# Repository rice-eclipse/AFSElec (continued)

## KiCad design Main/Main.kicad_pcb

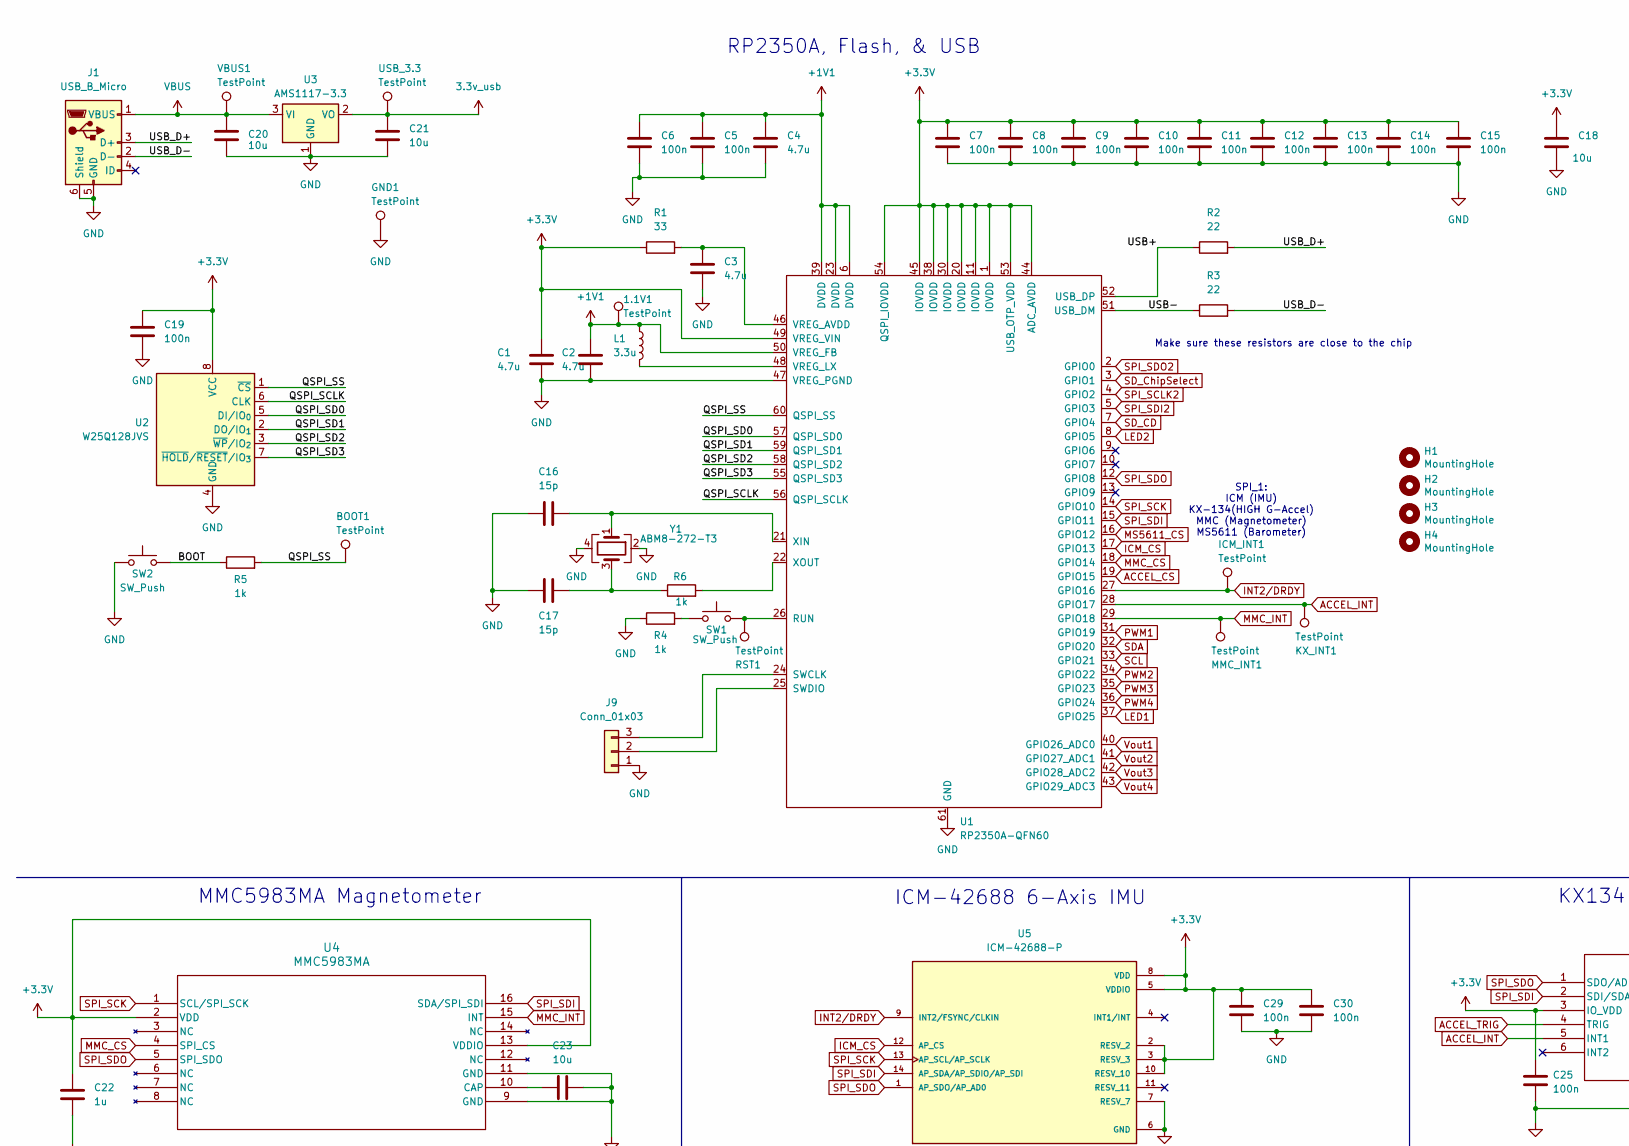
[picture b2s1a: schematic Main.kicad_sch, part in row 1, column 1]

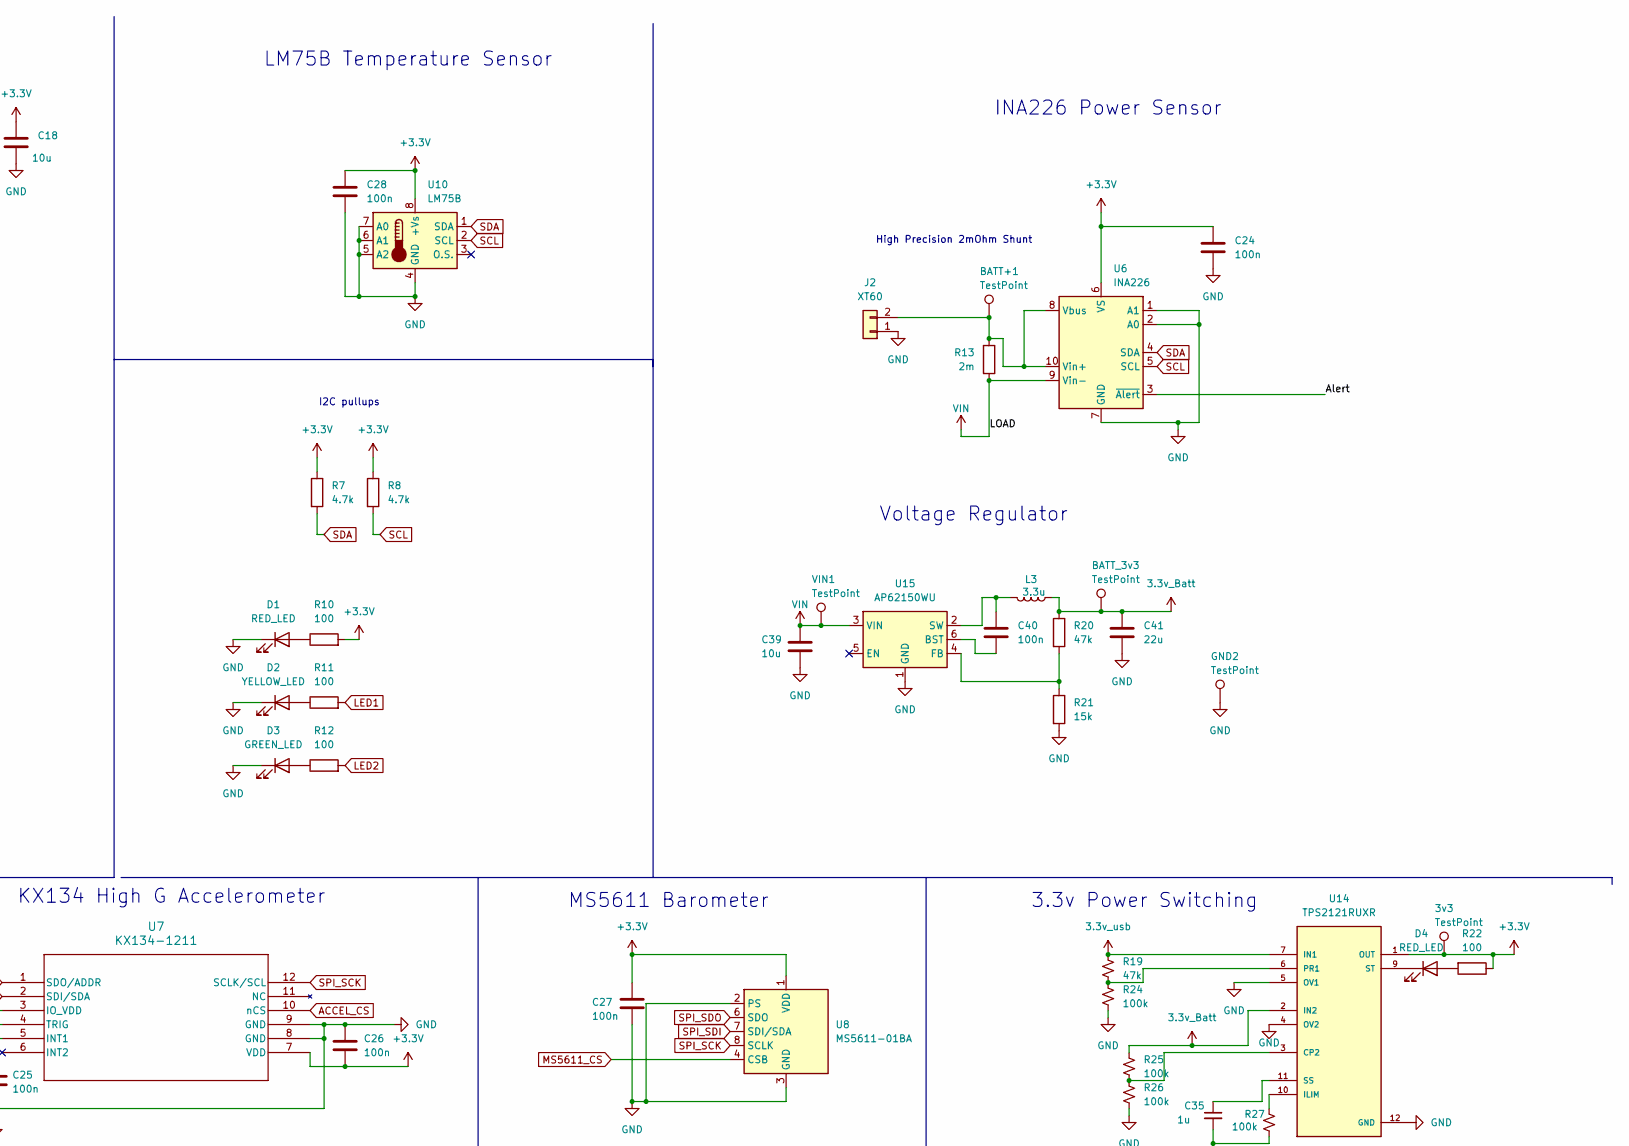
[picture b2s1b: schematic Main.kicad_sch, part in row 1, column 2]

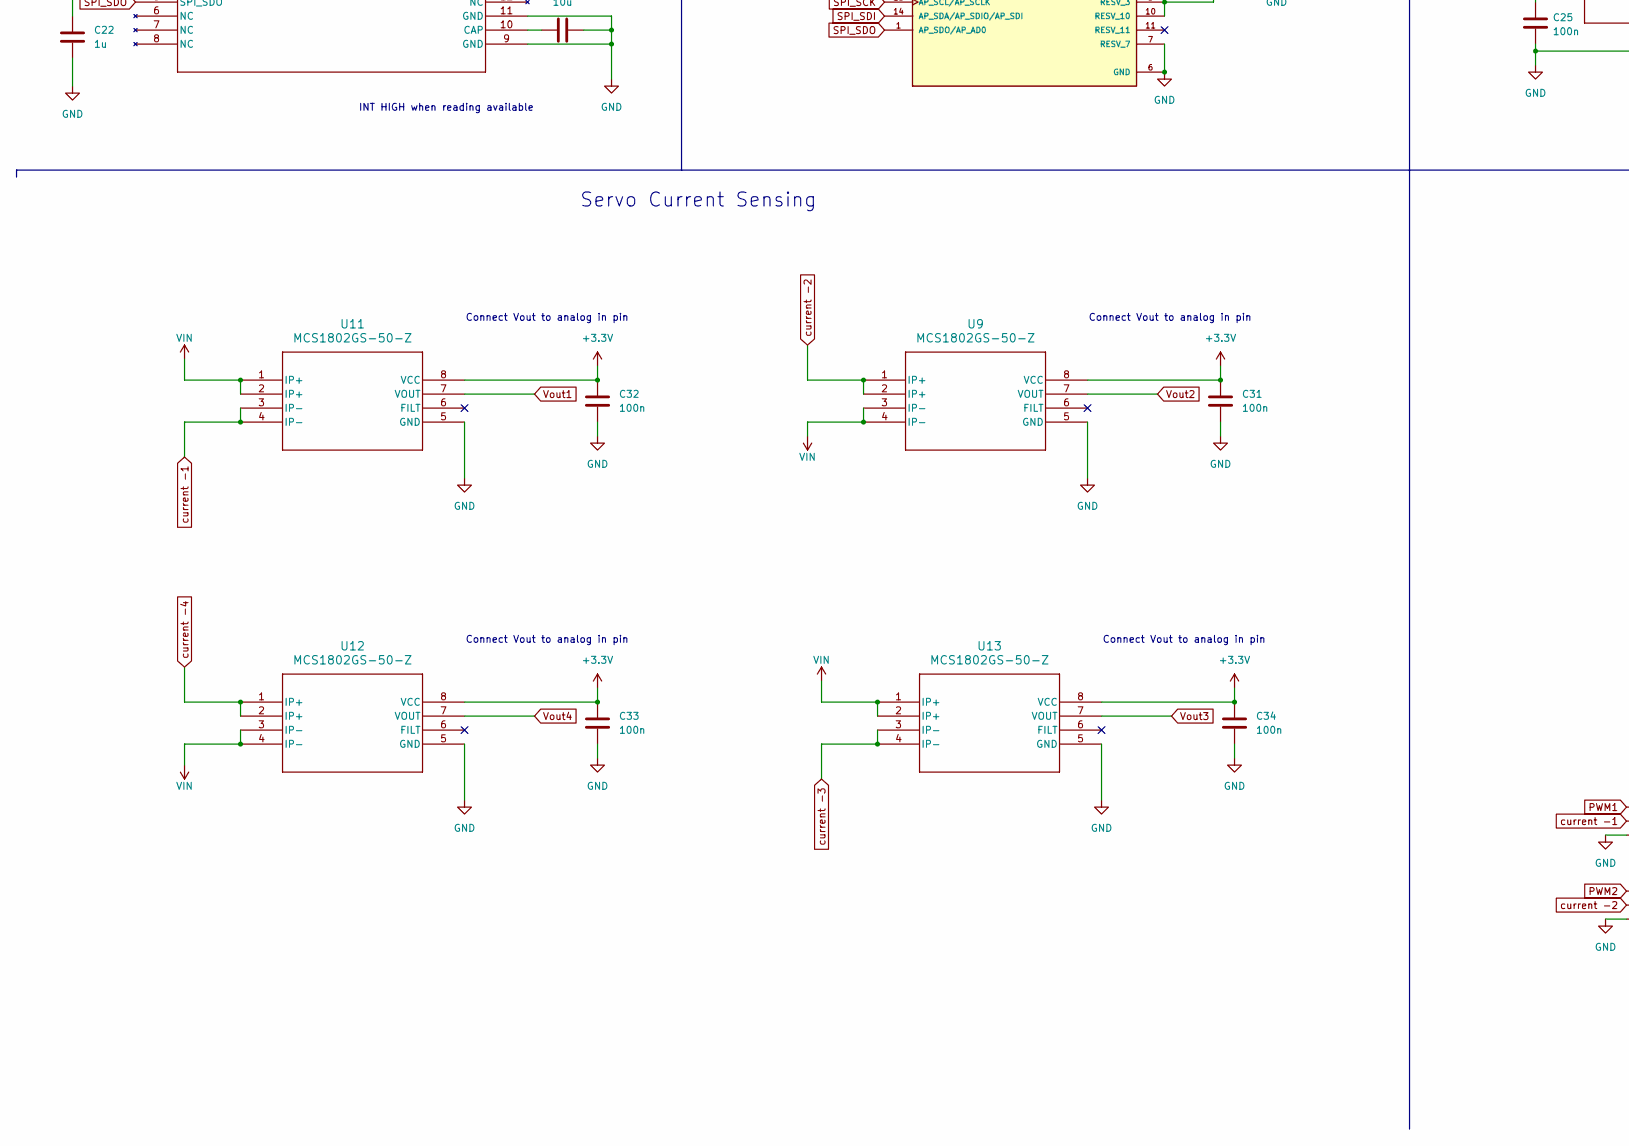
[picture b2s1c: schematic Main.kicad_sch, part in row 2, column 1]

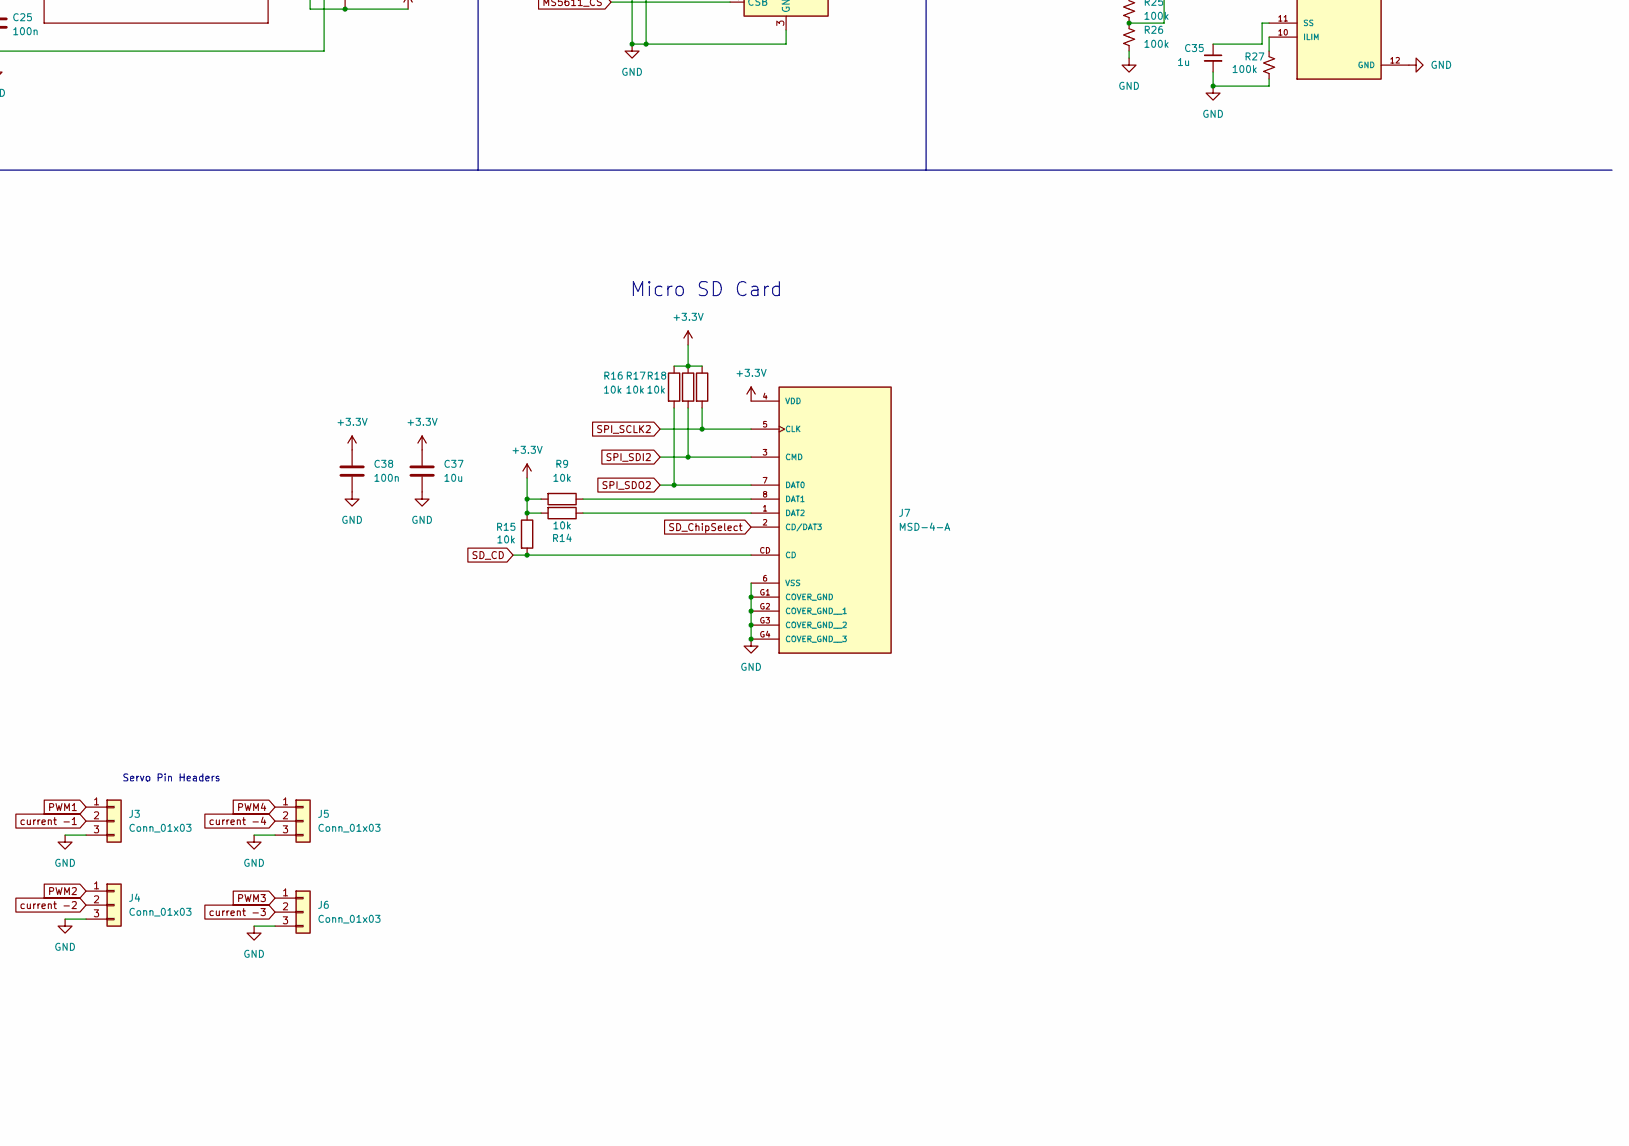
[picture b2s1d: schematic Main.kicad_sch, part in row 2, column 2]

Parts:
1.1V1, 3v3: TestPoint; TestPoint_Pad_D1.0mm
BATT+1: TestPoint; TestPoint_Pad_D1.0mm
BATT_3v3: TestPoint; TestPoint_Pad_D1.0mm
BOOT1: TestPoint; TestPoint_Pad_D1.0mm
C1, C2, C3, C4: 4.7u; C_0402_1005Metric; LCSC Part Number C23733
C5, C6, C7, C8, C9, C10, C11, C12, C13, C14, C15, C19, C24, C25, C26, C27, C28, C29, C30, C31, C32, C33, C34, C38, C40: 100n; C_0402_1005Metric; LCSC Part Number C1525
C16, C17: 15p; C_0402_1005Metric; LCSC Part Number C1548
C18, C20, C21, C23, C37: 10u; C_0805_2012Metric; LCSC Part Number C15850
C22, C35: 1u; C_0805_2012Metric; LCSC Part Number C28323
C39: 10u; C_0805_2012Metric; JLCPCB Part # C15850
C41: 22u; C_0805_2012Metric; LCSC Part Number C45783
D1, D4: RED_LED; LED_0805_2012Metric; LCSC Part Number C84256
D2: YELLOW_LED; LED_0805_2012Metric; LCSC Part Number C2296
D3: GREEN_LED; LED_0805_2012Metric; LCSC Part Number C2297
GND1, GND2: TestPoint; TestPoint_Pad_D1.0mm
H1, H2, H3, H4: MountingHole; MountingHole_3.2mm_M3_ISO14580_Pad
ICM_INT1: TestPoint; TestPoint_Pad_D1.0mm
J1: USB_B_Micro; USB_Micro-B_Amphenol_10118193-0001LF_Horizontal
J2: XT60; AMASS_XT60-M_1x02_P7.20mm_Vertical
J3, J4, J5, J6, J9: Conn_01x03; PinHeader_1x03_P2.54mm_Vertical
J7: MSD-4-A; CUI_MSD-4-A; PARTREV 1.0
KX_INT1: TestPoint; TestPoint_Pad_D1.0mm
L1, L3: 3.3u; AOTA-B201610S3R3-101-T(L_0806_2016metric)
MMC_INT1: TestPoint; TestPoint_Pad_D1.0mm
R1: 33; R_0402_1005Metric; LCSC Part Number C25105
R2, R3: 22; R_0402_1005Metric; LCSC Part Number C25092
R4, R5, R6: 1k; R_0402_1005Metric; LCSC Part Number C11702
R7, R8: 4.7k; R_0402_1005Metric; LCSC Part Number C25900
R9, R14, R15, R16, R17, R18: 10k; R_0402_1005Metric; LCSC Part Number C25744
R10, R11, R12, R22: 100; R_0402_1005Metric; LCSC Part Number C25076
R13: 2m; R_1206_3216Metric
R19, R20: 47k; R_0402_1005Metric; LCSC Part Number C25792
R21: 15k; R_0402_1005Metric; LCSC Part Number C25756
R24, R25, R26, R27: 100k; R_0402_1005Metric; LCSC Part Number C25741
RST1: TestPoint; TestPoint_Pad_D1.0mm
SW1, SW2: SW_Push; SW_Push_SPST_NO_Alps_SKRK
U1: RP2350A-QFN60; QFN-60-1EP_7x7mm_P0.4mm_EP3.4x3.4mm; LCSC Part Number C42411118
U2: W25Q128JVS; SOIC-8_5.3x5.3mm_P1.27mm; LCSC Part Number C97521
U3: AMS1117-3.3; SOT-223-3_TabPin2; LCSC Part Number C6186
U4: MMC5983MA; LGA-16_3x3mm_P0.5mm; LCSC Part Number C404329
U5: ICM-42688-P; LGA-14_3x2.5mm_P0.5mm_LayoutBorder3x4y; PARTREV 1.2; LCSC Part Number C48586483
U6: INA226; VSSOP-10_3x3mm_P0.5mm; LCSC Part Number C49851
U7: KX134-1211; LGA-12_2x2mm_P0.5mm; LCSC Part Number C2157908
U8: MS5611-01BA; LGA-8_3x5mm_P1.25mm; LCSC Part Number C15639
U9, U11, U12, U13: MCS1802GS-50-Z; SOIC-8-1EP_3.9x4.9mm_P1.27mm_EP2.29x3mm; LCSC Part Number C3684509
U10: LM75B; SOIC-8-1EP_3.9x4.9mm_P1.27mm_EP2.29x3mm; LCSC Part Number C34565
U14: TPS2121RUXR; Texas_VQFN-HR-12_2x2.5mm_P0.5mm; LCSC Part Number C485916
U15: AP62150WU; TSOT-23-6; LCSC Part Number C3194237
USB_3.3: TestPoint; TestPoint_Pad_D1.0mm
VBUS1: TestPoint; TestPoint_Pad_D1.0mm
VIN1: TestPoint; TestPoint_Pad_D1.0mm
Y1: ABM8-272-T3; Crystal_SMD_3225-4Pin_3.2x2.5mm; LCSC Part Number C20625731

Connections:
3.3v_Batt: BATT_3v3.1, C41.1, L3.1, R20.1, R25.1, U14.2 (IN2)
3.3v_usb: C21.1, R19.1, U3.2 (VO), U14.7 (IN1), USB_3.3.1
+1V1: 1.1V1.1, C2.1, C4.1, C5.1, C6.1, L1.1, U1.6 (DVDD), U1.23 (DVDD), U1.39 (DVDD), U1.50 (VREG_FB)
+3.3V: 3v3.1, C1.1, C7.1, C8.1, C9.1, C10.1, C11.1, C12.1, C13.1, C14.1, C15.1, C18.1, C19.1, C22.2, C24.1, C25.1, C26.2, C27.1, C28.1, C29.1, C30.1, C31.1, C32.1, C33.1, C34.1, C37.1, C38.1, J7.4 (VDD), R1.1, R7.1, R8.1, R9.2, R10.2, R14.2, R15.1, R16.1, R17.1, R18.1, R22.1, U1.1 (IOVDD), U1.11 (IOVDD), U1.20 (IOVDD), U1.30 (IOVDD), U1.38 (IOVDD), U1.44 (ADC_AVDD), U1.45 (IOVDD), U1.49 (VREG_VIN), U1.53 (USB_OTP_VDD), U1.54 (QSPI_IOVDD), U2.8 (VCC), U4.2 (VDD), U4.13 (VDDIO), U5.2 (RESV_2), U5.3 (RESV_3), U5.5 (VDDIO), U5.8 (VDD), U5.10 (RESV_10), U6.6 (VS), U7.3 (IO_VDD), U7.7 (VDD), U8.1 (VDD), U9.8 (VCC), U10.8 (+Vs), U11.8 (VCC), U12.8 (VCC), U13.8 (VCC), U14.1 (OUT), U14.8 (OUT)
/Alert: U6.3 (~Alert)
/BOOT: R5.1, SW2.2
/QSPI_SCLK: U1.56 (QSPI_SCLK), U2.6 (CLK)
/QSPI_SD0: U1.57 (QSPI_SD0), U2.5 (DI/IO_{0})
/QSPI_SD1: U1.59 (QSPI_SD1), U2.2 (DO/IO_{1})
/QSPI_SD2: U1.58 (QSPI_SD2), U2.3 (~WP/IO_{2})
/QSPI_SD3: U1.55 (QSPI_SD3), U2.7 (~HOLD/~RESET/IO_{3})
/QSPI_SS: BOOT1.1, R5.2, U1.60 (QSPI_SS), U2.1 (~CS); also elsewhere on the board
/USB+: R2.1, U1.52 (USB_DP)
/USB-: R3.1, U1.51 (USB_DM)
/USB_D+: J1.3 (D+), R2.2
/USB_D-: J1.2 (D-), R3.2
ACCEL_CS: U1.19 (GPIO15), U7.10 (nCS)
ACCEL_INT: KX_INT1.1, U1.28 (GPIO17), U7.5 (INT1); also elsewhere on the board
ACCEL_TRIG: U7.4 (TRIG)
GND: C1.2, C2.2, C3.2, C4.2, C5.2, C6.2, C7.2, C8.2, C9.2, C10.2, C11.2, C12.2, C13.2, C14.2, C15.2, C16.1, C17.1, C18.2, C19.2, C20.2, C21.2, C22.1, C23.2, C24.2, C25.2, C26.1, C27.2, C28.2, C29.2, C30.2, C31.2, C32.2, C33.2, C34.2, C35.2, C37.2, C38.2, C39.2, C41.2, D1.1 (K), D2.1 (K), D3.1 (K), GND1.1, GND2.1, H1.1, H2.1, H3.1, H4.1, J1.5 (GND), J1.6 (Shield), J2.1, J3.3, J4.3, J5.3, J6.3, J7.6 (VSS), J7.G1 (COVER_GND), J7.G2 (COVER_GND__1), J7.G3 (COVER_GND__2), J7.G4 (COVER_GND__3), J9.1, R4.1, R21.2, R24.2, R26.2, R27.2, SW2.1, U1.47 (VREG_PGND), U1.61 (GND), U2.4 (GND), U3.1 (GND), U4.9 (GND), U4.11 (GND), U5.6 (GND), U5.7 (RESV_7), U6.1 (A1), U6.2 (A0), U6.7 (GND), U7.8 (GND), U7.9 (GND), U8.2 (PS), U8.3 (GND), U9.5 (GND), U10.4 (GND), U10.5 (A2), U10.6 (A1), U10.7 (A0), U11.5 (GND), U12.5 (GND), U13.5 (GND), U14.4 (OV2), U14.5 (OV1), U14.12 (GND), U15.1 (GND), Y1.2, Y1.4; also elsewhere on the board
ICM_CS: U1.17 (GPIO13), U5.12 (AP_CS)
INT2/DRDY: ICM_INT1.1, U1.27 (GPIO16), U5.9 (INT2/FSYNC/CLKIN); also elsewhere on the board
LED1: R11.2, U1.37 (GPIO25)
LED2: R12.2, U1.8 (GPIO5)
MMC_CS: U1.18 (GPIO14), U4.4 (SPI_CS)
MMC_INT: MMC_INT1.1, U1.29 (GPIO18), U4.15 (INT); also elsewhere on the board
MS5611_CS: U1.16 (GPIO12), U8.4 (CSB), U8.5 (CSB)
unnamed: C17.2, R6.1, Y1.3
unnamed: D1.2 (A), R10.1
unnamed: D2.2 (A), R11.1
unnamed: D3.2 (A), R12.1
unnamed: D4.2 (A), R22.2
unnamed: D4.1 (K), U14.9 (ST)
unnamed 33: BATT+1.1, J2.2, R13.2, U6.8 (Vbus), U6.10 (Vin+); also elsewhere on the board
unnamed: J7.8 (DAT1), R9.1
unnamed: J7.1 (DAT2), R14.1
unnamed: J9.2, U1.25 (SWDIO)
unnamed: J9.3, U1.24 (SWCLK)
unnamed: R4.2, SW1.1
unnamed 39: RST1.1, SW1.2, U1.26 (RUN); also elsewhere on the board
unnamed: C3.1, R1.2, U1.46 (VREG_AVDD)
unnamed: L1.2, U1.48 (VREG_LX)
unnamed: C16.2, U1.21 (XIN), Y1.1
unnamed: R6.2, U1.22 (XOUT)
unnamed: C23.1, U4.10 (CAP)
unnamed: R25.2, R26.1, U14.3 (CP2)
unnamed: R27.1, U14.10 (ILIM)
unnamed: R19.2, R24.1, U14.6 (PR1)
unnamed: C35.1, U14.11 (SS)
unnamed: C40.2, U15.6 (BST)
unnamed: R20.2, R21.1, U15.4 (FB)
unnamed: C40.1, L3.2, U15.2 (SW)
PWM1: J3.1, U1.31 (GPIO19)
PWM2: J4.1, U1.34 (GPIO22)
PWM3: J6.1, U1.35 (GPIO23)
PWM4: J5.1, U1.36 (GPIO24)
SCL: R8.2, U1.33 (GPIO21), U6.5 (SCL), U10.2 (SCL)
SDA: R7.2, U1.32 (GPIO20), U6.4 (SDA), U10.1 (SDA)
SD_CD: J7.CD, R15.2, U1.7 (GPIO4)
SD_ChipSelect: J7.2 (CD/DAT3), U1.3 (GPIO1)
SPI_SCK: U1.14 (GPIO10), U4.1 (SCL/SPI_SCK), U5.13 (AP_SCL/AP_SCLK), U7.12 (SCLK/SCL), U8.8 (SCLK)
SPI_SCLK2: J7.5 (CLK), R18.2, U1.4 (GPIO2)
SPI_SDI: U1.15 (GPIO11), U4.16 (SDA/SPI_SDI), U5.14 (AP_SDA/AP_SDIO/AP_SDI), U7.2 (SDI/SDA), U8.7 (SDI/SDA)
SPI_SDI2: J7.3 (CMD), R17.2, U1.5 (GPIO3)
SPI_SDO: U1.12 (GPIO8), U4.5 (SPI_SDO), U5.1 (AP_SDO/AP_AD0), U7.1 (SDO/ADDR), U8.6 (SDO)
SPI_SDO2: J7.7 (DAT0), R16.2, U1.2 (GPIO0)
VBUS: C20.1, J1.1 (VBUS), U3.3 (VI), VBUS1.1; also elsewhere on the board
VIN: C39.1, R13.1, U6.9 (Vin-), U9.3 (IP-), U9.4 (IP-), U11.1 (IP+), U11.2 (IP+), U12.3 (IP-), U12.4 (IP-), U13.1 (IP+), U13.2 (IP+), U15.3 (VIN), VIN1.1; also elsewhere on the board
Vout1: U1.40 (GPIO26_ADC0), U11.7 (VOUT)
Vout2: U1.41 (GPIO27_ADC1), U9.7 (VOUT)
Vout3: U1.42 (GPIO28_ADC2), U13.7 (VOUT)
Vout4: U1.43 (GPIO29_ADC3), U12.7 (VOUT)
current -1: J3.2, U11.3 (IP-), U11.4 (IP-)
current -2: J4.2, U9.1 (IP+), U9.2 (IP+)
current -3: J6.2, U13.3 (IP-), U13.4 (IP-)
current -4: J5.2, U12.1 (IP+), U12.2 (IP+)

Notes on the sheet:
MMC5983MA Magnetometer
I2C pullups
RP2350A, Flash, & USB
Servo Current Sensing
Servo Pin Headers
Connect Vout to analog in pin
LM75B Temperature Sensor
SPI_1: ICM (IMU) KX-134(HIGH G-Accel) MMC (Magnetometer) MS5611 (Barometer)
Voltage Regulator
High Precision 2mOhm Shunt
INT HIGH when reading available
Micro SD Card
INA226 Power Sensor
ICM-42688 6-Axis IMU
KX134 High G Accelerometer
MS5611 Barometer
3.3v Power Switching
Make sure these resistors are close to the chip

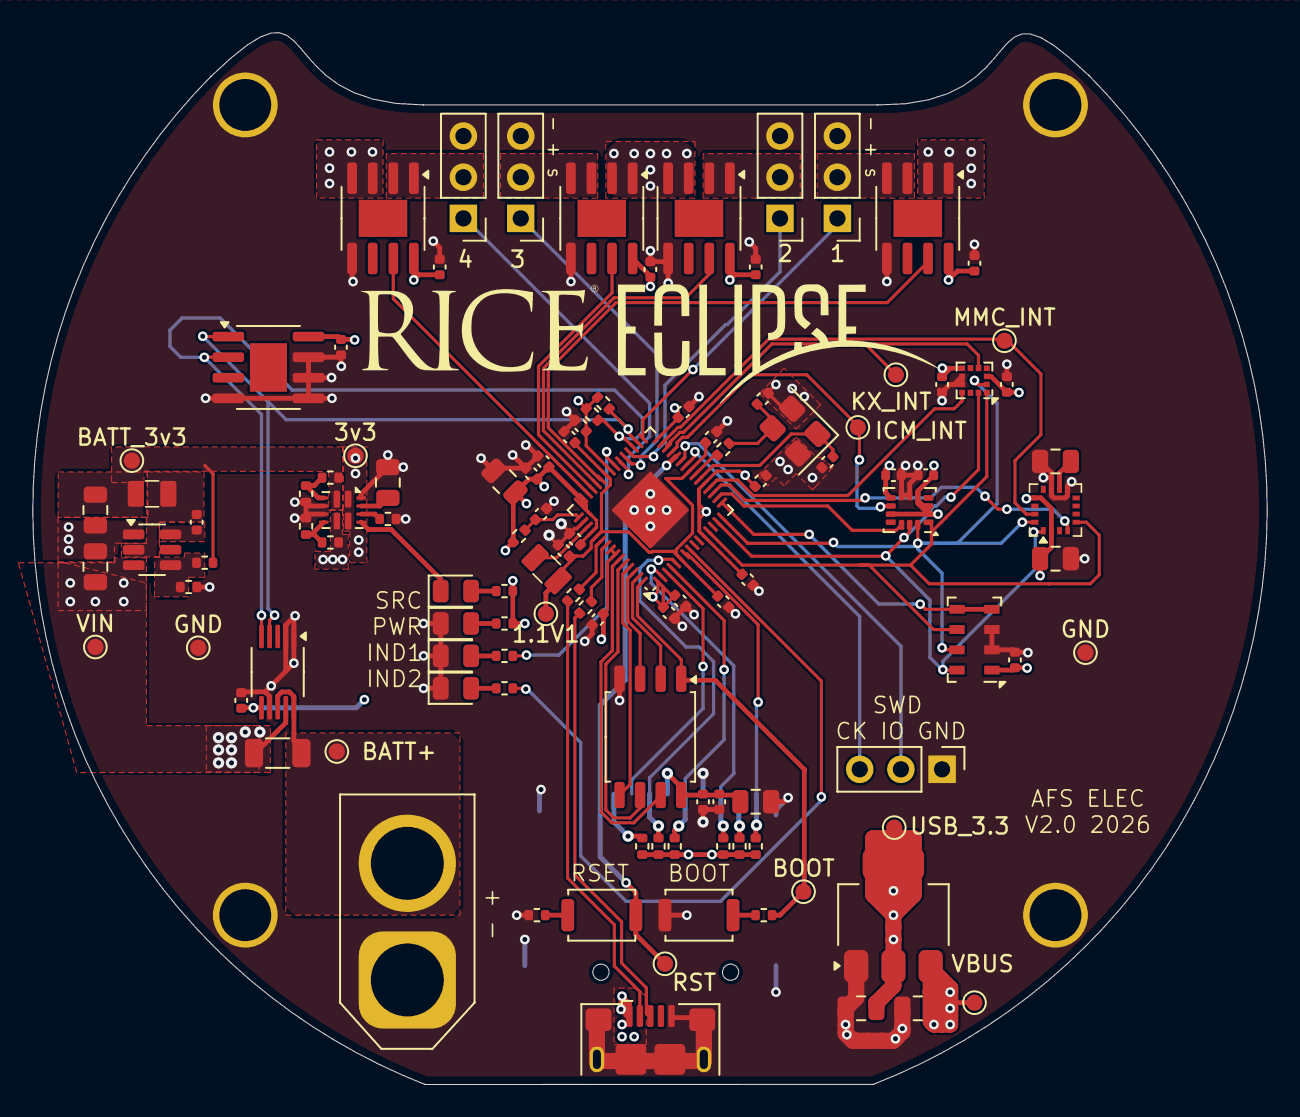
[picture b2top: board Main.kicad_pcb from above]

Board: 4 copper layers, 76.2 x 64.9 mm, 116 parts (1 on the bottom side), 74 nets.

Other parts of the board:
BATT+: TestPoint; TestPoint_Pad_D1.0mm
BOOT: TestPoint; TestPoint_Pad_D1.0mm
GND: TestPoint; TestPoint_Pad_D1.0mm
GND#2: TestPoint; TestPoint_Pad_D1.0mm
ICM_INT: TestPoint; TestPoint_Pad_D1.0mm
KX_INT: TestPoint; TestPoint_Pad_D1.0mm
MMC_INT: TestPoint; TestPoint_Pad_D1.0mm
RST: TestPoint; TestPoint_Pad_D1.0mm
VBUS: TestPoint; TestPoint_Pad_D1.0mm
VIN: TestPoint; TestPoint_Pad_D1.0mm

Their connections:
/QSPI_SS: BOOT.1; also elsewhere on the board
ACCEL_INT: KX_INT.1; also elsewhere on the board
GND: GND.1, GND#2.1; also elsewhere on the board
INT2/DRDY: ICM_INT.1; also elsewhere on the board
MMC_INT: MMC_INT.1; also elsewhere on the board
unnamed 33: BATT+.1; also elsewhere on the board
unnamed 39: RST.1; also elsewhere on the board
VBUS: VBUS.1; also elsewhere on the board
VIN: VIN.1; also elsewhere on the board

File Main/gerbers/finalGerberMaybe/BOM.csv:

"Designator","Qty","Comment","Footprint","LCSC Part Number"
"1.1V1,3v3,BATT+1,BATT_3v3,BOOT1,GND1,GND2,ICM_INT1,KX_INT1,MMC_INT1,RST1,USB_3.3,VBUS1,VIN1","14","TestPoint","TestPoint:TestPoint_Pad_D1.0mm",""
"C1,C2,C3,C4","4","4.7u","Capacitor_SMD:C_0402_1005Metric","C23733"
"C5,C6,C7,C8,C9,C10,C11,C12,C13,C14,C15,C19,C24,C25,C26,C27,C28,C29,C30,C31,C32,C33,C34,C38,C40","25","100n","Capacitor_SMD:C_0402_1005Metric","C1525"
"C16,C17","2","15p","Capacitor_SMD:C_0402_1005Metric","C1548"
"C18,C20,C21,C23,C37,C39","6","10u","Capacitor_SMD:C_0805_2012Metric","C15850"
"C22,C35","2","1u","Capacitor_SMD:C_0805_2012Metric","C28323"
"C41","1","22u","Capacitor_SMD:C_0805_2012Metric","C45783"
"D1,D4","2","RED_LED","LED_SMD:LED_0805_2012Metric","C84256"
"D2","1","YELLOW_LED","LED_SMD:LED_0805_2012Metric","C2296"
"D3","1","GREEN_LED","LED_SMD:LED_0805_2012Metric","C2297"
"H1,H2,H3,H4","4","MountingHole","MountingHole:MountingHole_3.2mm_M3_ISO14580_Pad",""
"J1","1","USB_B_Micro","Connector_USB:USB_Micro-B_Amphenol_10118193-0001LF_Horizontal",""
"J2","1","XT60","Connector_AMASS:AMASS_XT60-M_1x02_P7.20mm_Vertical",""
"J3,J4,J5,J6,J9","5","Conn_01x03","Connector_PinHeader_2.54mm:PinHeader_1x03_P2.54mm_Vertical",""
"J7","1","MSD-4-A","otherComponents:CUI_MSD-4-A",""
"L1,L3","2","3.3u","otherComponents:AOTA-B201610S3R3-101-T(L_0806_2016metric)",""
"R1","1","33","Resistor_SMD:R_0402_1005Metric","C25105"
"R2,R3","2","22","Resistor_SMD:R_0402_1005Metric","C25092"
"R4,R5,R6","3","1k","Resistor_SMD:R_0402_1005Metric","C11702"
"R7,R8","2","4.7k","Resistor_SMD:R_0402_1005Metric","C25900"
"R9,R14,R15,R16,R17,R18","6","10k","Resistor_SMD:R_0402_1005Metric","C25744"
"R10,R11,R12,R22","4","100","Resistor_SMD:R_0402_1005Metric","C25076"
"R13","1","2m","Resistor_SMD:R_1206_3216Metric",""
"R19,R20","2","47k","Resistor_SMD:R_0402_1005Metric","C25792"
"R21","1","15k","Resistor_SMD:R_0402_1005Metric","C25756"
"R24,R25,R26,R27","4","100k","Resistor_SMD:R_0402_1005Metric","C25741"
"SW1,SW2","2","SW_Push","Button_Switch_SMD:SW_Push_SPST_NO_Alps_SKRK",""
"U1","1","RP2350A-QFN60","Package_DFN_QFN:QFN-60-1EP_7x7mm_P0.4mm_EP3.4x3.4mm","C42411118"
"U2","1","W25Q128JVS","Package_SO:SOIC-8_5.3x5.3mm_P1.27mm","C97521"
"U3","1","AMS1117-3.3","Package_TO_SOT_SMD:SOT-223-3_TabPin2","C6186"
"U4","1","MMC5983MA","Package_LGA:LGA-16_3x3mm_P0.5mm","C404329"
"U5","1","ICM-42688-P","Package_LGA:LGA-14_3x2.5mm_P0.5mm_LayoutBorder3x4y","C48586483"
"U6","1","INA226","Package_SO:VSSOP-10_3x3mm_P0.5mm","C49851"
"U7","1","KX134-1211","Package_LGA:LGA-12_2x2mm_P0.5mm","C2157908"
"U8","1","MS5611-01BA","Package_LGA:LGA-8_3x5mm_P1.25mm","C15639"
"U9,U11,U12,U13","4","MCS1802GS-50-Z","Package_SO:SOIC-8-1EP_3.9x4.9mm_P1.27mm_EP2.29x3mm","C3684509"
"U10","1","LM75B","Package_SO:SOIC-8-1EP_3.9x4.9mm_P1.27mm_EP2.29x3mm","C34565"
"U14","1","TPS2121RUXR","Package_DFN_QFN:Texas_VQFN-HR-12_2x2.5mm_P0.5mm","C485916"
"U15","1","AP62150WU","Package_TO_SOT_SMD:TSOT-23-6","C3194237"
"Y1","1","ABM8-272-T3","Crystal:Crystal_SMD_3225-4Pin_3.2x2.5mm","C20625731"

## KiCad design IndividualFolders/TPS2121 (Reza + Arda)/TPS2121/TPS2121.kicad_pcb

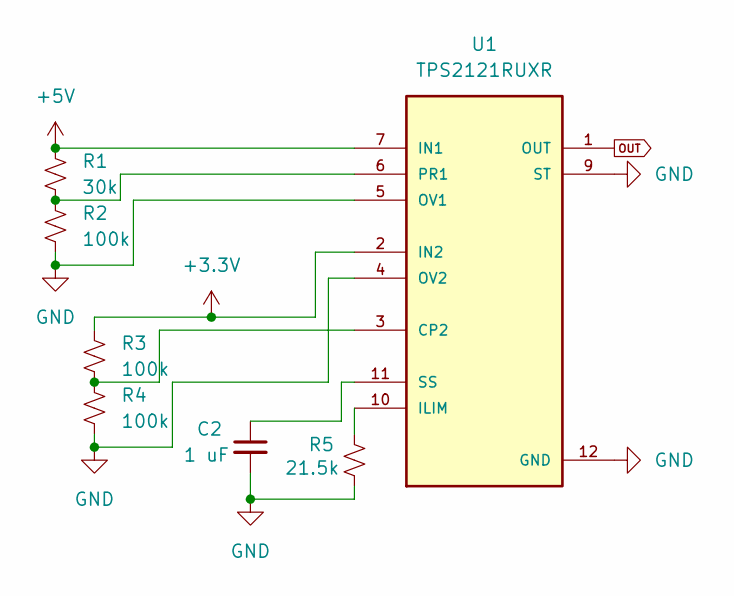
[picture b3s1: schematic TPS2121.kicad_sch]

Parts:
C2: 1 uF; C_0805_2012Metric
R1: 30k; R_0805_2012Metric
R2, R3, R4: 100k; R_0805_2012Metric
R5: 21.5k; R_0805_2012Metric
U1: TPS2121RUXR; IC_TPS2121RUXR

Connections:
+3.3V: R3.1, U1.2 (IN2), U1.2_1 (IN2)
+5V: R1.1, U1.7 (IN1), U1.7_1 (IN1)
GND: C2.2, R2.2, R4.2, R5.2, U1.4 (OV2), U1.5 (OV1), U1.9 (ST), U1.12 (GND)
unnamed: R3.2, R4.1, U1.3 (CP2)
unnamed: R5.1, U1.10 (ILIM)
unnamed: R1.2, R2.1, U1.6 (PR1)
unnamed: C2.1, U1.11 (SS)
OUT: U1.1 (OUT), U1.1_1 (OUT), U1.8 (OUT), U1.8_1 (OUT)

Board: 2 copper layers, 7 parts (0 on the bottom side), 8 nets, no tracks yet.

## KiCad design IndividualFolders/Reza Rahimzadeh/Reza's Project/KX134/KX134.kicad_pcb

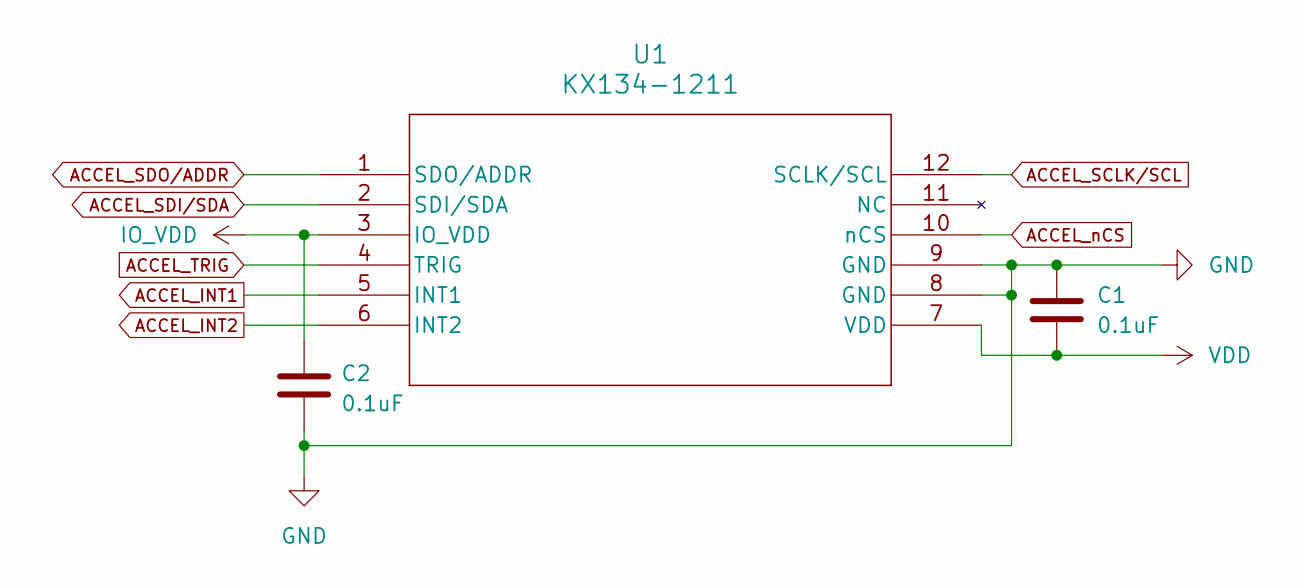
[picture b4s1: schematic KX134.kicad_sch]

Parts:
C1, C2: 0.1uF; C_0805_2012Metric
U1: KX134-1211; LGA-12_2x2mm_P0.5mm

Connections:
ACCEL_INT1: U1.5 (INT1)
ACCEL_INT2: U1.6 (INT2)
ACCEL_SCLK/SCL: U1.12 (SCLK/SCL)
ACCEL_SDI/SDA: U1.2 (SDI/SDA)
ACCEL_SDO/ADDR: U1.1 (SDO/ADDR)
ACCEL_TRIG: U1.4 (TRIG)
ACCEL_nCS: U1.10 (nCS)
GND: C1.1, C2.2, U1.8 (GND), U1.9 (GND)
IO_VDD: C2.1, U1.3 (IO_VDD)
VDD: C1.2, U1.7 (VDD)

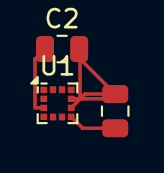
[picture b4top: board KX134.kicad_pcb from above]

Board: 2 copper layers, 3 parts (0 on the bottom side), 3 nets.

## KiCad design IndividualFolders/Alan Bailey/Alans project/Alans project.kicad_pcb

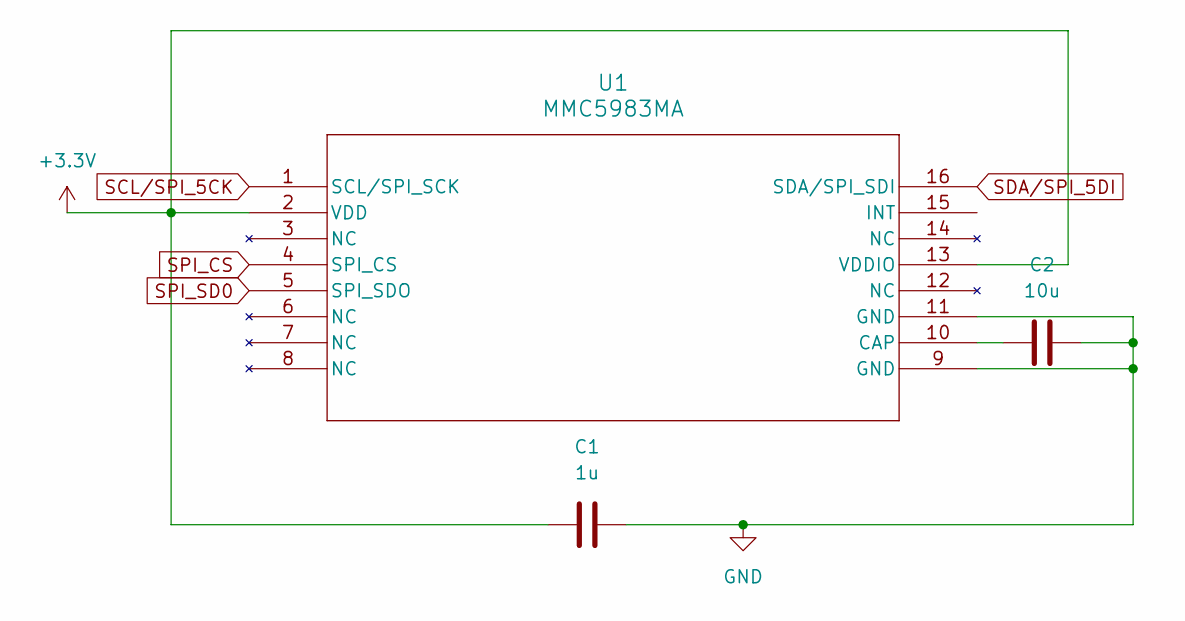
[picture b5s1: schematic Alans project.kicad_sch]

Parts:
C1: 1u; C_0805_2012Metric
C2: 10u; C_0805_2012Metric
U1: MMC5983MA; LGA-16_3x3mm_P0.5mm

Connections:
+3.3V: C1.1, U1.2 (VDD), U1.13 (VDDIO)
GND: C1.2, C2.2, U1.9 (GND), U1.11 (GND)
unnamed: C2.1, U1.10 (CAP)
SCL/SPI_5CK: U1.1 (SCL/SPI_SCK)
SDA/SPI_5DI: U1.16 (SDA/SPI_SDI)
SPI_CS: U1.4 (SPI_CS)
SPI_SD0: U1.5 (SPI_SDO)

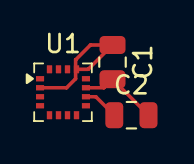
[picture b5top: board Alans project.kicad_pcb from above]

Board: 2 copper layers, 3 parts (0 on the bottom side), 3 nets.

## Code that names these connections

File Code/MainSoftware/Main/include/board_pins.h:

/**
 * board_pins.h - GPIO map for the AFS electronics board (Version2, RP2350B QFN-80).
 *
 * "Pin" comments are the RP2350B package pad numbers (U2 in Version2.kicad_pcb), which differ from
 * GPIO numbers wherever IOVDD pads sit in between (e.g. GPIO24 is pad 25).
 */
#pragma once

#include "pico/types.h"
#include "hardware/spi.h"
#include "hardware/i2c.h"
#include "hardware/uart.h"

// ============================================================================
// General-purpose GPIO
// ============================================================================
constexpr uint GPIO_00 = 0; // Pin 77
constexpr uint GPIO_01 = 1; // Pin 78
constexpr uint GPIO_02 = 2; // Pin 79
constexpr uint GPIO_03 = 3; // Pin 80

// ============================================================================
// PWM outputs
// ============================================================================
constexpr uint PWM2 = 6;  // Pin 3
constexpr uint PWM3 = 7;  // Pin 4
constexpr uint PWM1 = 8;  // Pin 6
constexpr uint PWM4 = 9;  // Pin 7
constexpr uint PWM8 = 44; // Pin 55
constexpr uint PWM7 = 45; // Pin 56
constexpr uint PWM5 = 46; // Pin 57
constexpr uint PWM6 = 47; // Pin 58

// ============================================================================
// External I2C (I2C 2 connector) - GPIO 10/11 = i2c1
// ============================================================================
#define EXT_I2C i2c1
constexpr uint SDA2 = 10; // Pin 8
constexpr uint SCL2 = 11; // Pin 9

// ============================================================================
// UART0 - GPIO 12/13 = uart0
// ============================================================================
#define BOARD_UART uart0
constexpr uint UART0_TX = 12; // Pin 11
constexpr uint UART0_RX = 13; // Pin 12

// ============================================================================
// Onboard sensors
// ============================================================================
// Sensor SPI bus - GPIO 16-19 = spi0 (ICM45686, KX134, MMC5983MA, MS5611, extra CS)
#define SENSOR_SPI spi0
constexpr uint SPI_MISO_SEN = 16; // Pin 16
constexpr uint SPI_SCK_SEN  = 18; // Pin 18
constexpr uint SPI_MOSI_SEN = 19; // Pin 19

constexpr uint IMU_CS      = 17; // Pin 17  ICM45686
constexpr uint BAR_CS      = 20; // Pin 20  MS5611
constexpr uint MAG_CS      = 21; // Pin 21  MMC5983MA
constexpr uint ACC_CS      = 22; // Pin 22  KX134
constexpr uint XTRA_SPI_CS = 27; // Pin 28  spare

constexpr uint IMU_INT1 = 15; // Pin 14  ICM45686 INT1
constexpr uint MAG_INT  = 23; // Pin 23  MMC5983MA INT
constexpr uint ACC_INT  = 26; // Pin 27  KX134 INT1

/** Every chip select on the sensor SPI bus (drive all high before using the bus). */
constexpr uint SENSOR_SPI_CS_PINS[] = {IMU_CS, ACC_CS, MAG_CS, BAR_CS, XTRA_SPI_CS};

// Onboard I2C - GPIO 24/25 = i2c0 (TMP117, INA219)
#define SENSOR_I2C i2c0
constexpr uint SDA = 24; // Pin 25
constexpr uint SCL = 25; // Pin 26 (visual label on schematic shows 25/26)

// ============================================================================
// SD card - GPIO 28-31 = spi1
// ============================================================================
#define SD_SPI spi1
constexpr uint SPI_MISO_SD    = 28; // Pin 36
constexpr uint SD_CHIP_SELECT = 29; // Pin 37
constexpr uint SPI_SCK_SD     = 30; // Pin 38
constexpr uint SPI_MOSI_SD    = 31; // Pin 39
constexpr uint SD_CHIP_DETECT = 35; // Pin 44

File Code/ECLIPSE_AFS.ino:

/*
RICE ECLISPE AFS Basic Code


*/
//sensor libraries
#include <Temperature_LM75_Derived.h>
#include <INA226.h>

//other libraries
#include <Wire.h>

//pin definitions
#define led1 25 //yellow indicator led - can also use LED_BUILTIN instead of led1
#define led2 5 //green indicator led

#define current1 26//4 current detecting pins for servos
#define current2 27
#define current3 28
#define current4 29

#define PWM1 19 //pwm pins
#define PWM2 22
#define PWM3 23
#define PWM4 24

#define I2C_SDA 20 //I2C pins
#define I2C_SCL 21

#define SPI_SDO 8 //sensor SPI pins
#define SPI_SDI 11
#define SPI_SCK 10

#define IMU_CS 13 //6 axis IMU SPI select pin 
#define MAG_CS 14 //3 axis Magnetometer SPI select pin 
#define ACC_CS 15 //3 axis high g accelerometer SPI select pin 
#define BAR_CS 12 //barometer SPI select pin 

//whether to print things or not, printing will slow down program so turn off for real testing maybe?
int debug = true;

//define sensors
Generic_LM75 temperatureSensor;
INA226 INA(0x40);


void setup() {
  // initialize pin modes
  pinMode(led1, OUTPUT);
  pinMode(led2, OUTPUT);

  pinMode(current1, INPUT);
  pinMode(current2, INPUT);
  pinMode(current3, INPUT);
  pinMode(current4, INPUT);

  pinMode(PWM1, OUTPUT);
  pinMode(PWM2, OUTPUT);
  pinMode(PWM3, OUTPUT);
  pinMode(PWM4, OUTPUT);

  

  // Wait for Serial to initialize
  while(!Serial) {
    delay(10);
  }
  
  //begin serial monitor
  if (debug){
    Serial.begin(115200);
  }

  // Configure RP2350 pins for I2C1
  // GPIO 20 = SDA, GPIO 21 = SCL
  Wire.setSDA(I2C_SDA);
  Wire.setSCL(I2C_SCL);
  Wire.begin();

  //setup INA226
  if (!INA.begin() )
  {
    Serial.println("could not connect to INA226. Fix and Reboot");
  }
  INA.setMaxCurrentShunt(15, 0.002);
}

//storing of values
double temp;

double currDraw1;
double currDraw2;
double currDraw3;
double currDraw4;

double batteryVoltage;
double shuntVoltage;
double currentDraw;
double powerDraw;


void updateData(){
  temp = temperatureSensor.readTemperatureC();

  currDraw1 = map(analogRead(current1),0,1023,-5000,5000)/1000.0;
  currDraw2 = map(analogRead(current2),0,1023,-5000,5000)/1000.0;
  currDraw3 = map(analogRead(current3),0,1023,-5000,5000)/1000.0;
  currDraw4 = map(analogRead(current4),0,1023,-5000,5000)/1000.0;

  batteryVoltage = INA.getBusVoltage();
  shuntVoltage = INA.getShuntVoltage_mV();
  currentDraw = INA.getCurrent_mA();
  powerDraw = INA.getPower_mW();

}


void loop() {
  updateData();
  
  if (debug){
    Serial.print("Temperature = ");
    Serial.print(temp,1);
    Serial.print(" C, ");

    Serial.print("Power Draw = ");
    Serial.print(powerDraw,3);
    Serial.print(" mW, ");

    Serial.println();


  }
  
}

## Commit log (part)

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2026-01-21 make test file
2026-01-21 made a change
2026-01-21 said hi to alan
2026-01-21 Add README with project information and contribution guidelines
2026-01-21 Added main, Clarified Test
2026-01-23 Said Hi
2026-01-23 hello
2026-01-23 Created Folder For Everyone
2026-01-23 Frieren.
2026-01-23 Create Selected.png
    Richard added folder
2026-01-23 removed
2026-01-23 Wiping Everything
2026-01-23 Update README to highlight contribution guidelines
    Emphasize the importance of following contribution guidelines and provide a link to the documentation.
2026-01-23 individual folders
2026-01-23 Make Alan's project file
2026-01-29 Added Logo
2026-02-02 landons changes
2026-02-02 Made the recommended circuit for the MMC5983MA
2026-02-02 Get rid of temporary editing file
2026-02-02 Created the recommended circuit for the KX134
2026-02-02 Updated KX134 Schematic
2026-02-05 Implement INA226 typical application
2026-02-05 Update INA226 schematic
2026-02-05 implement ms5611 schematic
    I implemented the ms5611 schematic
2026-02-05 LM75B Schematic
2026-02-05 RP2350 Typical Schematic Added
2026-02-06 Created individual folder
2026-02-06 mcs1802 current sensor typical application
    sigma sigma
2026-02-06 Create Temp Sensor-2026-02-05_181801.zip
    !!!
2026-02-06 Copy schematics to one folder
2026-02-06 Voltage Regular Schematic
2026-02-06 moveSchematics
2026-02-08 RENAMED SHIT TO WORK
2026-02-08 add footprint and make basic pcb
2026-02-08 Select footprint's and make basic PCB for KX134
2026-02-08 Assign footprints
2026-02-08 Choose footprints for LM2575 power regulator. May need to be changed. HIGH POWER
2026-02-08 mcs1802
2026-02-08 Barometer PCB (and footprints) done
2026-02-13 Updated footprints
2026-02-13 Fixes and Additions
    Added current sensors for servos, fixed a few schematics for each chip, and made slight stylistic edits
2026-02-14 Added servo connectors and micro SD
2026-02-15 added leds
2026-02-17 Started Layout
2026-02-17 Layout/Footprint Updates
    updated footprint of inductor for R-Pi, started planning layout for R-PI components in middle of board, added two options for board size
2026-02-17 More RP2350 Footprint
    put more footprints in place(mostly power), updated things to 0402 where possible, and added switching regulator to schematic
2026-02-19 Added 3rd board outline option
    new outline without servo cutouts but with one servo wiring hole
2026-02-19 Added shunt footprint and small changes
2026-02-20 updated before meeting
2026-02-20 added button footprint
2026-02-20 updated usb footprint
2026-02-20 SD and USB footprint and model updated
2026-02-20 added xt60 connector
2026-02-23 ready for schematic planning
    still no sd card circuit/components for regulator but we can plan more where everything goes
2026-02-23 Worked on PCB Layout Prototype
2026-02-23 Individual main
2026-02-23 pls dont break
2026-02-23 Main PCB Layout
2026-02-23 02/22 Reza PCB Design
2026-02-23 changed name to hopefully pull correctly
2026-02-23 added schematic sd card
2026-02-23 added p-channel mosfet for power control
    USB plugged in -> VBUS high, Vgs on mosfet = 0 -> mosfet off, disconect linear regulator from 3.3v system rails
2026-02-24 changed voltage regulator
    new voltage regulator chip(smaller + more effecient) and supporting components
2026-02-24 some layout stuff
2026-02-24 more layout updates and small fixes
2026-02-25 more layout updates
2026-02-26 updated layout
2026-02-26 Power Reg Layout Complete
2026-02-26 ready for meeting updates
2026-02-27 TPS2121 Schematic & Footprints
2026-02-27 updated power switching schematic
    still need to fix footprint tsp
2026-02-27 make a version of the PCB
    dont think it's right
2026-02-27 Meeting 2/28/26
2026-02-27 updated power switching circuit
2026-02-27 updated power circuit layout
2026-03-01 Main PCB practice wiring
2026-03-01 idk man
2026-03-01 Wiring Mostly Done
2026-03-01 Add capacitor part numbers
2026-03-01 Resistor component numbers
2026-03-01 PART NUMBERSSSSS
2026-03-01 Basically Ready
    Yippeeee
2026-03-02 changed a few components for manufacturing
2026-03-02 Changed resistor values to be basic JLC components
2026-03-02 lowkey had pwm wire labeled wrong(fixed now)
2026-03-03 changed 2 jlcpcb part numbers
2026-03-03 Added place for serial number
    JLCJLCJLCJLC text is replaced by manufacturer with serial number upon order
2026-03-03 added test points
2026-03-12 Added some labeled on the schematic
2026-03-26 Added Code
2026-03-26 updated code
2026-03-26 Create ICM42688GeminiDebug.ino
    Gemini Debug
2026-03-27 Update ICM42688GeminiDebugV2.ino
    Gemini V2
2026-03-27 Working ICM42688 Code
    YAY
2026-03-27 made some baro progress
2026-03-30 make basic library
2026-03-30 move it
2026-03-30 update library so that user can set accelerometer and gyroscope range when initalizing the IMU
2026-03-30 testFailed
2026-03-30 fix it
2026-03-30 make it work (hopefully)
2026-03-30 small change
2026-04-09 Moves the spi transactions to the begin function as this caused errors upon instantiation
2026-04-09 ChangesFUCKKKKKKKKKKKKKKKKK
2026-04-10 Library fixes
    not fully working yet, but progress
2026-04-10 zener diode demo
